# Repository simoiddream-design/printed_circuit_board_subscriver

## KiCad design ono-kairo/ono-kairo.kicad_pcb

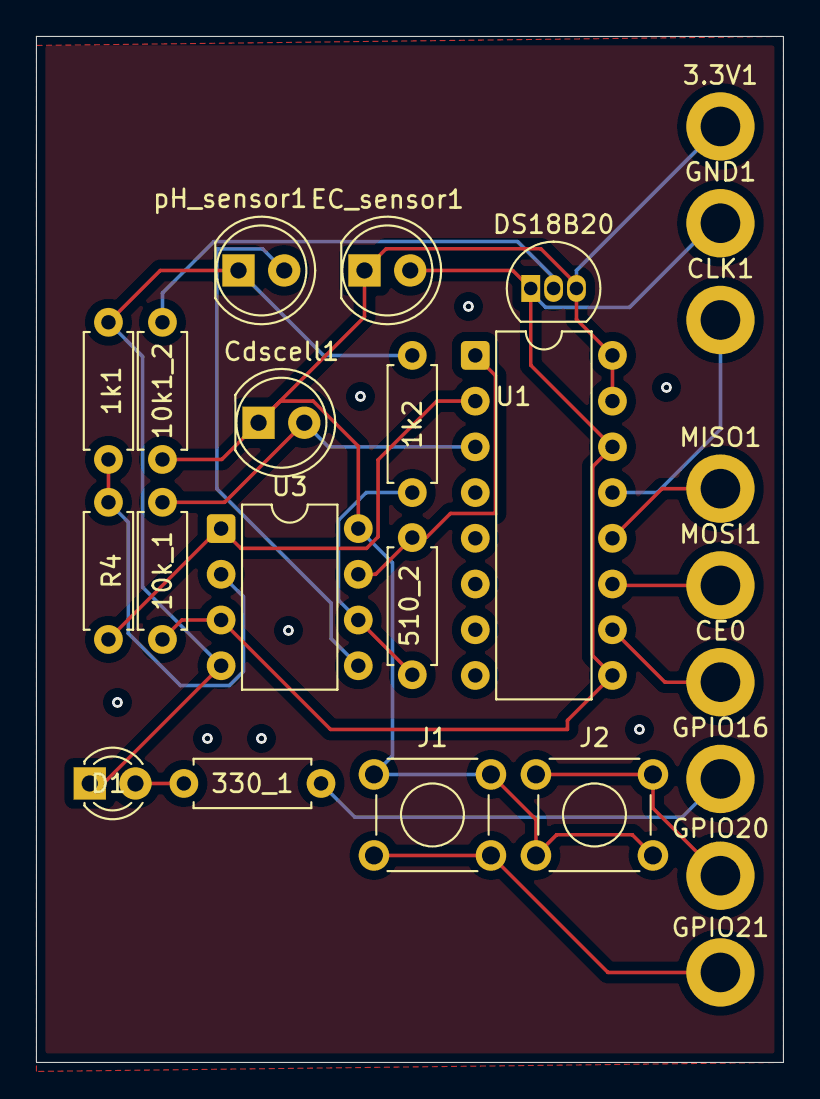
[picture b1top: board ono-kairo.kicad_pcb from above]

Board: 2 copper layers, 41.5 x 57.0 mm, 25 parts (0 on the bottom side), 17 nets.

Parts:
1k1, 1k2: 1k; R_Axial_DIN0207_L6.3mm_D2.5mm_P7.62mm_Horizontal
3.3V1: 3.3V; MountingHole_2.2mm_M2_DIN965_Pad
10k1_2, 10k_1: 10k; R_Axial_DIN0207_L6.3mm_D2.5mm_P7.62mm_Horizontal
330_1: 330; R_Axial_DIN0207_L6.3mm_D2.5mm_P7.62mm_Horizontal
510_2: 510; R_Axial_DIN0207_L6.3mm_D2.5mm_P7.62mm_Horizontal
CE0: CE0; MountingHole_2.2mm_M2_DIN965_Pad
CLK1: CLK; MountingHole_2.2mm_M2_DIN965_Pad
Cdscell1: R; LED_D5.0mm
D1: LED; LED_D3.0mm
DS18B20: DS18B20; TO-92_Inline
EC_sensor1: R; LED_D5.0mm
GND1: GND; MountingHole_2.2mm_M2_DIN965_Pad
GPIO16: gpio16; MountingHole_2.2mm_M2_DIN965_Pad
GPIO20: gpio20; MountingHole_2.2mm_M2_DIN965_Pad
GPIO21: gpio21; MountingHole_2.2mm_M2_DIN965_Pad
J1: Conn; SW_TH_Tactile_Omron_B3F-107x
J2: Bottom; SW_TH_Tactile_Omron_B3F-107x
MISO1: MISO; MountingHole_2.2mm_M2_DIN965_Pad
MOSI1: MOSI; MountingHole_2.2mm_M2_DIN965_Pad
R4: 510; R_Axial_DIN0207_L6.3mm_D2.5mm_P7.62mm_Horizontal
U1: MCP3208; DIP-16_W7.62mm
U3: MCP6002-xMC; DIP-8_W7.62mm
pH_sensor1: R; LED_D5.0mm

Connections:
unnamed: 330_1.2, GPIO16.1
unnamed: 330_1.1, D1.2 (A)
unnamed: 1k1.2, 1k2.2, 10k_1.2, D1.1 (K), DS18B20.1 (GND), EC_sensor1.2, GND1.1, U1.9 (DGND), U1.14 (AGND), U3.3 (+), U3.4 (V-), pH_sensor1.1
unnamed: 10k1_2.2, DS18B20.2 (DQ)
unnamed: 3.3V1.1, 10k1_2.1, Cdscell1.1, DS18B20.3 (V_{DD}), EC_sensor1.1, J1.1, J2.2, U1.15 (Vref), U1.16 (Vdd), U3.8 (V+)
unnamed: GPIO21.1, J1.2
unnamed: GPIO20.1, J2.1
unnamed: 510_2.1, U1.1 (CH0), U3.7
unnamed: R4.1, U1.2 (CH1), U3.1
unnamed: 10k_1.1, Cdscell1.2, U1.3 (CH2)
unnamed: CLK1.1, U1.13 (CLK)
unnamed: MOSI1.1, U1.11 (Din)
unnamed: MISO1.1, U1.12 (Dout)
unnamed: CE0.1, U1.10 (~CS/SHDN)
unnamed: 1k1.1, R4.2, U3.2 (-)
unnamed: U3.5 (+), pH_sensor1.2
unnamed: 1k2.1, 510_2.2, U3.6 (-)
